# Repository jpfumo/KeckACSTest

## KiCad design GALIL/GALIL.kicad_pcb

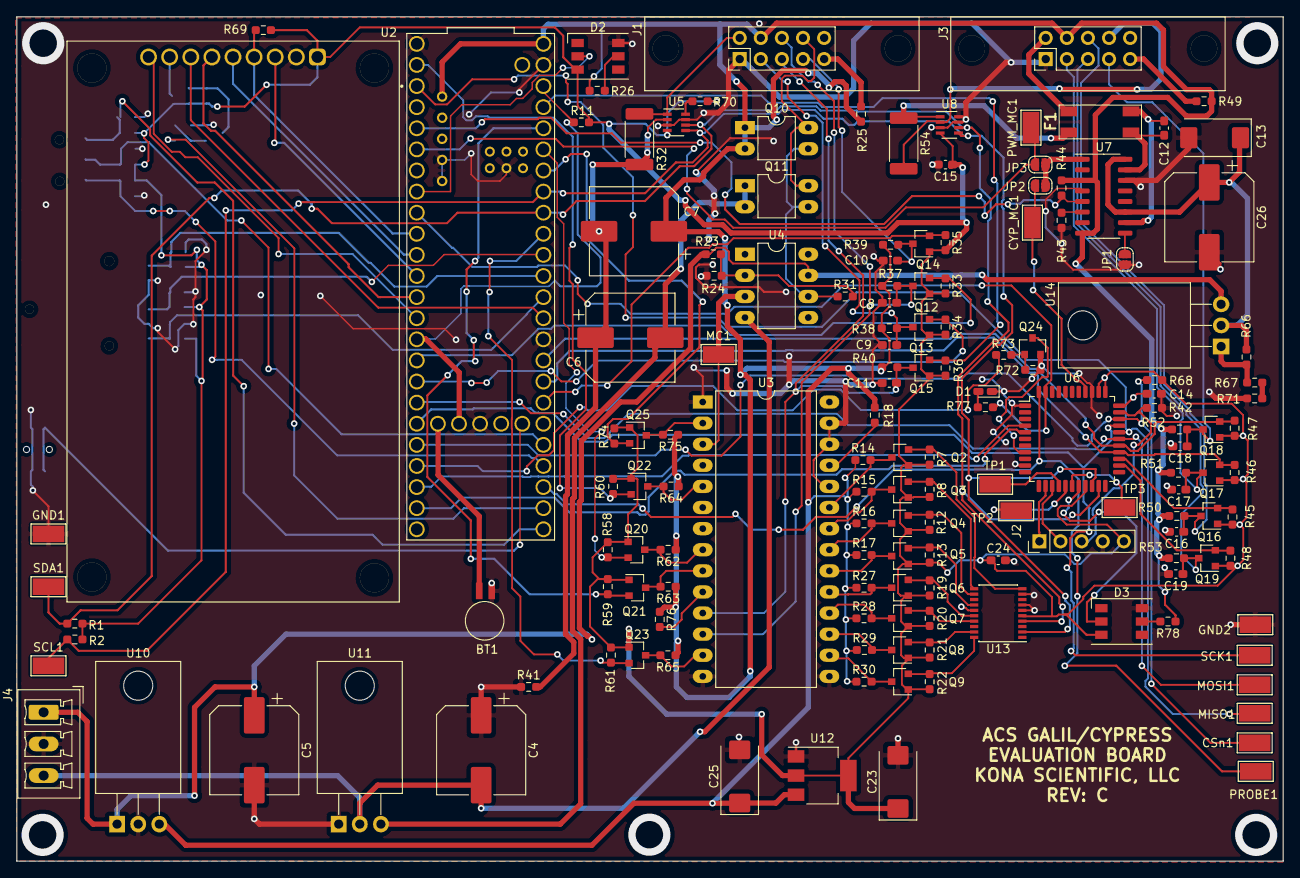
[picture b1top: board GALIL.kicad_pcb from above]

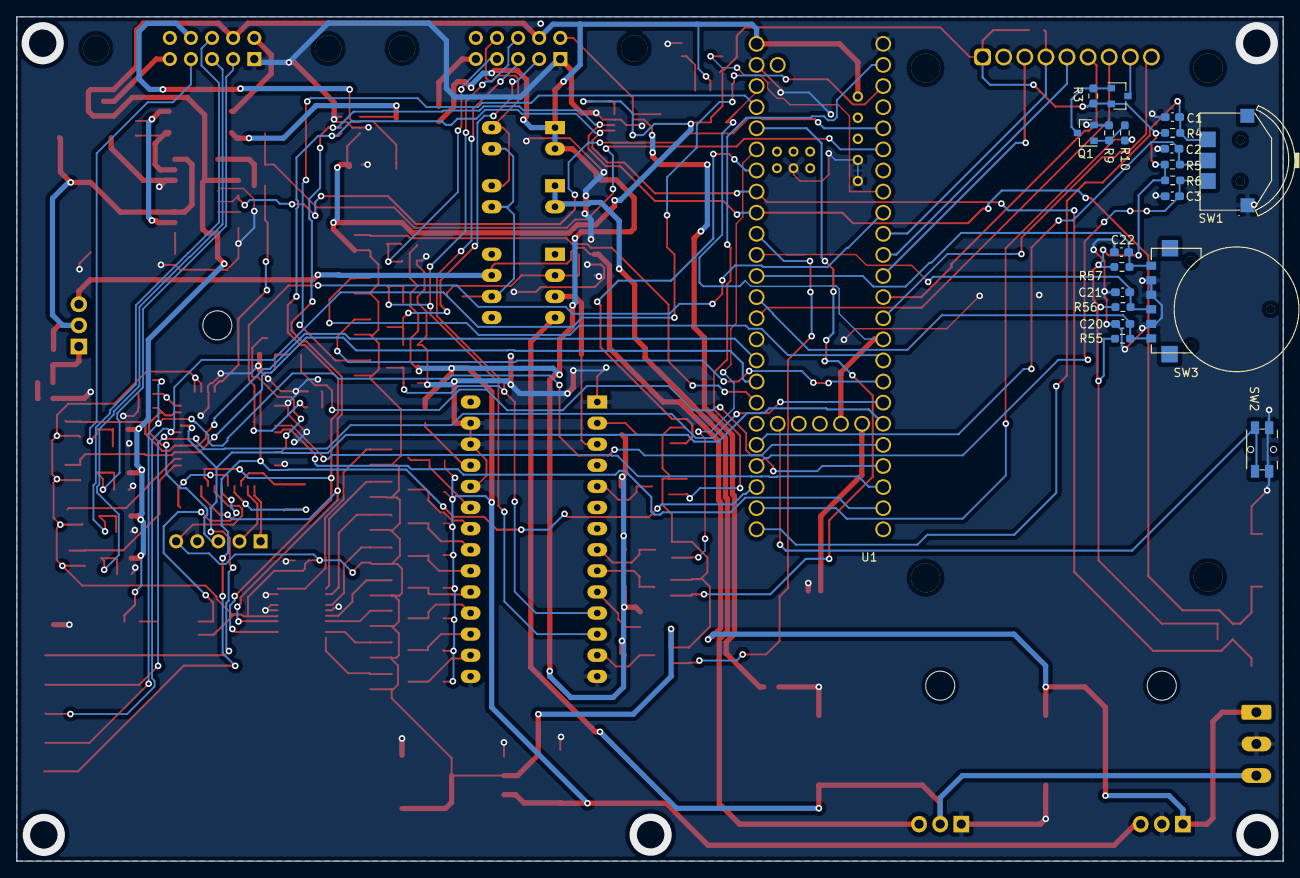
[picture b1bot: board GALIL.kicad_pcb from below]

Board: 2 copper layers, 152.4 x 101.6 mm, 173 parts (21 on the bottom side), 117 nets.

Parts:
BT1: Battery_Cell; BatteryHolder_Seiko_MS621F
C1, C2, C3: 0U1; C_0603_1608Metric_Pad1.08x0.95mm_HandSolder
C4, C5, C6, C7, C26: CP; CP_Elec_10x10.5
C8, C9, C10, C11, C16, C17, C18, C19, C20, C21, C22, C24: C; C_0603_1608Metric_Pad1.08x0.95mm_HandSolder
C12: 2200pF; C_0603_1608Metric_Pad1.08x0.95mm_HandSolder
C13: 740mF; CP_EIA-7343-15_Kemet-W
C14, C15: 1uF; C_0603_1608Metric_Pad1.08x0.95mm_HandSolder
C23, C25: CP; CP_EIA-7343-20_Kemet-V_Pad2.25x2.55mm_HandSolder
CSn1: CSn; TestPoint_Keystone_5019_Minature
CYP_MC1: TestPoint; TestPoint_Keystone_5019_Minature
D1: LED; LED_0603_1608Metric_Castellated
D2, D3: WS2812S; LED_WS2812_PLCC6_5.0x5.0mm_P1.6mm
F1: 744229; WE-SL575
GND1, GND2: TestPoint; TestPoint_Keystone_5019_Minature
J1, J3: Conn_01x10; StrutConn
J2: Conn_01x05; PinHeader_1x05_P2.54mm_Vertical
J4: Conn_01x03; PhoenixContact_MCV_1,5_3-G-3.81_1x03_P3.81mm_Vertical
JP1, JP2, JP3: SolderJumper_2_Open; SolderJumper-2_P1.3mm_Open_RoundedPad1.0x1.5mm
MC1: TestPoint; TestPoint_Keystone_5019_Minature
MISO1: MISO; TestPoint_Keystone_5019_Minature
MOSFET1: FDN358P; SOT-23
MOSI1: MOSI; TestPoint_Keystone_5019_Minature
PROBE1: PROBE; TestPoint_Keystone_5019_Minature
PWM_MC1: TestPoint; TestPoint_Keystone_5019_Minature
Q1, Q24: MMBT3904; SOT-23
Q2, Q3, Q4, Q5, Q6, Q7, Q8, Q9, Q12, Q13, Q14, Q15, Q16, Q17, Q18, Q19, Q20, Q21, Q22, Q23, Q25: BSS138; SOT-23
Q10: IRFD110; DIP-4_W7.62mm_LongPads
Q11: IRFD9102; DIP-4_W7.62mm_LongPads
R1, R2: 4K75; R_0603_1608Metric_Pad0.98x0.95mm_HandSolder
R3, R4, R5, R6, R9, R55, R56, R57, R68, R69, R72, R76: 10K0; R_0603_1608Metric_Pad0.98x0.95mm_HandSolder
R7, R8, R12, R13, R14, R15, R16, R17, R19, R20, R21, R22, R27, R28, R29, R30, R58, R59, R60, R61, R62, R63, R64, R65, R74, R75: R; R_0603_1608Metric_Pad0.98x0.95mm_HandSolder
R10, R73: 1K0; R_0603_1608Metric_Pad0.98x0.95mm_HandSolder
R11: DNP; R_0603_1608Metric_Pad0.98x0.95mm_HandSolder
R18, R24, R33, R34, R35, R36, R37, R38, R39, R40, R42, R44, R45, R46, R47, R48, R50, R51, R52, R53, R70: 10K; R_0603_1608Metric_Pad0.98x0.95mm_HandSolder
R23: 130K; R_0603_1608Metric_Pad0.98x0.95mm_HandSolder
R25, R49, R77: 120ohms 1/4W; R_0603_1608Metric_Pad0.98x0.95mm_HandSolder
R26, R78: 100R0; R_0603_1608Metric_Pad0.98x0.95mm_HandSolder
R31: 68K; R_0603_1608Metric_Pad0.98x0.95mm_HandSolder
R32: 1R0; R_2512_6332Metric_Pad1.40x3.35mm_HandSolder
R41: 0R0; R_0603_1608Metric_Pad0.98x0.95mm_HandSolder
R43: 5K; R_0603_1608Metric_Pad0.98x0.95mm_HandSolder
R54: 1.0; R_2512_6332Metric_Pad1.40x3.35mm_HandSolder
R66: 120; R_0603_1608Metric_Pad0.98x0.95mm_HandSolder
R67: 906; R_0603_1608Metric_Pad0.98x0.95mm_HandSolder
R71: 54; R_0603_1608Metric_Pad0.98x0.95mm_HandSolder
SCK1: SCK; TestPoint_Keystone_5019_Minature
SCL1: SCL; TestPoint_Keystone_5019_Minature
SDA1: SDA; TestPoint_Keystone_5019_Minature
SW1: SEL_SW
SW2: SW_Push; Panasonic_EVQPUL_EVQPUC
SW3: EVQ-WKA001
TP1, TP2, TP3: TP; TestPoint_Keystone_5019_Minature
U1: DEV-16771; teensy41
U2: TFT_LCD; TFT_DISP_2P2
U3: GALIL; DIP-28_W15.24mm_LongPads
U4: TL081; DIP-8_W7.62mm_LongPads
U5, U8: INA219AxDCN; SOT-23-8
U6: CY8C4245AXI-483; LQFP-44_10x10mm_P0.8mm
U7: SI8244; SO-16_3.9x9.9mm_P1.27mm
U10: LM7805_TO220; TO-220-3_Horizontal_TabDown
U11: LM7905_TO220; TO-220-3_Horizontal_TabDown
U12: LT1117-3.3; SOT-223-3_TabPin2
U13: PCF8574ATS; SSOP-20_4.4x6.5mm_P0.65mm
U14: LM350_TO220; TO-220-3_Horizontal_TabDown

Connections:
+3V3: C15.1, C23.1, C24.1, D2.3, D3.3, J2.5, MOSFET1.2, Q2.1, Q3.1, Q4.1, Q5.1, Q6.1, Q7.1, Q8.1, Q9.1, Q12.1, Q13.1, Q14.1, Q15.1, Q16.1, Q17.1, Q18.1, Q19.1, Q20.1, Q21.1, Q22.1, Q23.1, Q25.1, R1.1, R2.1, R3.1, R4.1, R5.1, R6.1, R7.1, R8.1, R11.1, R12.1, R13.1, R19.1, R20.1, R21.1, R22.1, R33.2, R34.2, R35.2, R36.2, R45.2, R46.2, R47.2, R48.2, R55.2, R56.2, R57.2, R58.1, R59.1, R60.1, R61.1, R68.1, R69.1, R70.2, R74.1, U2.1, U5.4, U6.19, U6.34, U6.35, U8.4, U12.2, U13.5
+5V: C7.1, C25.1, J1.4, J3.4, Q10.1, Q10.2, R14.1, R15.1, R16.1, R17.1, R18.2, R25.1, R26.1, R27.1, R28.1, R29.1, R30.1, R37.2, R38.2, R39.2, R40.2, R44.1, R49.1, R50.2, R51.2, R52.2, R53.2, R62.1, R63.1, R64.1, R65.1, R75.1, R76.1, R78.1, U1.5V, U1.VIN, U7.3, U7.8, U10.3, U12.3
+15V: C5.1, J4.1, R23.2, U4.7, U10.1, U14.3
-5V: C6.2, Q11.1, Q11.2, U11.3
-15V: C4.2, J4.3, U4.4, U11.2
BL_EN: MOSFET1.1, Q1.3, R3.2
CLED: D3.2, U6.18
CS: U1.10, U2.3
CYPRESS_PWM0: CYP_MC1.1, JP2.2, U6.37
CYP_CSn: CSn1.1, R68.2, U1.28, U6.31
CypressRST_MOT0: Q24.3, U6.8
Cypress_DebugReset0: J2.3, R42.1, U6.32
DC: U1.9, U2.5
ENC1_A: C19.1, J3.5, Q19.3, R53.1
ENC1_A_L: Q19.2, R48.1, U6.24
ENC1_B: C16.1, J3.6, Q16.3, R50.1
ENC1_B_L: Q16.2, R45.1, U6.25
ENC1_HOME: C17.1, J3.3, Q17.3, R51.1
ENC1_HOME_L: Q17.2, R46.1, U1.40, U6.26
ENC1_HOME_OUT: U1.30, U6.4
ENC1_INDEX: C18.1, J3.7, Q18.3, R52.1
ENC1_INDEX_L: Q18.2, R47.1, U1.41, U6.27
ENC1_INDEX_OUT: U1.31, U6.5
ENC1_MTR1: F1.3, R54.1, U8.1
ENC1_MTR2: F1.4, J3.2
ENC1_MTR_RTN: JP1.1, U7.9
ENC2_A: C11.1, J1.5, Q15.3, R40.1, U3.11
ENC2_A_L: Q15.2, R36.1, U1.23
ENC2_B: C8.1, J1.6, Q12.3, R37.1, U3.12
ENC2_B_L: Q12.2, R33.1, U1.24
ENC2_HOME: C9.1, J1.3, Q13.3, R38.1
ENC2_HOME_L: Q13.2, R34.1, U1.25
ENC2_INDEX: C10.1, J1.7, Q14.3, R39.1
ENC2_INDEX_L: Q14.2, R35.1, U1.39
ENC2_MTR1: J1.8, Q10.4, Q11.4
ENC2_MTR2: J1.2, R32.1, U5.1
GALIL_CLK: Q22.2, R60.2, U1.0
GALIL_CLK_HV: Q22.3, R64.2, U3.5
GALIL_DEC: Q20.2, R58.2, U1.21
GALIL_DEC_HV: Q20.3, R62.2, U3.8
GALIL_ERR_FLG: Q25.2, R74.2, U1.20
GALIL_ERR_FLG_HV: Q25.3, R75.2, U3.2
GALIL_INC: Q21.2, R59.2, U1.22
GALIL_INC_HV: Q21.3, R63.2, U3.9
GALIL_PE0: Q2.2, R7.2, U13.10
GALIL_PE1: Q3.2, R8.2, U13.11
GALIL_PE2: Q4.2, R12.2, U13.12
GALIL_PE3: Q5.2, R13.2, U13.14
GALIL_PE4: Q6.2, R19.2, U13.16
GALIL_PE5: Q7.2, R20.2, U13.17
GALIL_PE6: Q8.2, R21.2, U13.19
GALIL_PE7: Q9.2, R22.2, U13.20
GALIL_RSTn: Q23.2, R61.2, U1.17
GALIL_RSTn_HV: Q23.3, R65.2, U3.13
GND: BT1.2, C1.1, C2.1, C3.1, C4.1, C5.2, C8.2, C9.2, C10.2, C11.2, C13.2, C14.1, C15.2, C16.2, C17.2, C18.2, C19.2, C20.2, C21.2, C22.2, C23.2, C24.2, C25.2, C26.2, D1.1, D2.6, D3.6, GND1.1, GND2.1, J1.1, J2.4, J3.1, J4.2, JP1.2, Q1.2, Q24.2, R9.2, R24.1, R41.1, R42.2, R43.2, R71.2, R72.2, SW1.5, SW2.1, SW3.2, SW3.3, SW3.5, U1.GND1, U1.GND2, U1.GND3, U1.GND4, U1.GND5, U1.USB_GND1, U1.USB_GND2, U2.2, U3.1, U3.14, U3.15, U3.24, U3.26, U3.27, U5.3, U5.7, U6.1, U6.10, U6.36, U7.4, U7.14, U8.3, U8.7, U8.8, U10.2, U11.1, U12.1, U13.6, U13.7, U13.9, U13.15
GNDPWR: C6.1, C7.2, R32.2, R41.2, U5.2
HV_GALIL_PE0: Q2.3, R14.2, U3.23
HV_GALIL_PE1: Q3.3, R15.2, U3.22
HV_GALIL_PE2: Q4.3, R16.2, U3.21
HV_GALIL_PE3: Q5.3, R17.2, U3.20
HV_GALIL_PE4: Q6.3, R27.2, U3.19
HV_GALIL_PE5: Q7.3, R28.2, U3.18
HV_GALIL_PE6: Q8.3, R29.2, U3.17
HV_GALIL_PE7: Q9.3, R30.2, U3.16
I2C_SCL: R2.2, SCL1.1, U1.19, U5.5, U6.20, U8.5, U13.2
I2C_SDA: R1.2, SDA1.1, U1.18, U5.6, U6.21, U8.6, U13.4
LED: R77.2, U1.7, U6.43
MISO: U1.12, U2.9
MISO1: MISO1.1, U1.1, U6.29
MOSI: U1.11, U2.6
MOSI1: MOSI1.1, U1.26, U6.28
Motor_Cntrl: MC1.1, U3.3, U4.3
NEOPIXEL: D2.2, U1.6
unnamed: BT1.1, U1.VBAT
unnamed: C12.1, F1.1, U7.10
unnamed: C12.2, F1.2, U7.15
unnamed: C14.2, U6.33
unnamed: D1.2, R77.1
unnamed: D2.5, R26.2
unnamed: D3.5, R78.2
unnamed: J1.9, R25.2
unnamed: J2.1, U6.13
unnamed: J2.2, U6.14
unnamed: J3.8, R54.2, U8.2
unnamed: J3.9, R49.2
unnamed: JP2.1, JP3.1, U7.1
unnamed: MOSFET1.3, U2.8
unnamed: Q1.1, R9.1, R10.2
unnamed: Q10.3, Q11.3, R31.1, U4.6
unnamed: Q24.1, R72.1, R73.2
unnamed: R10.1, U1.34
unnamed: R11.2, U1.3.3V_1, U1.3.3V_2, U1.3.3V_3
unnamed: R18.1, U3.25
unnamed: R23.1, R24.2, R31.2, U4.2
unnamed: R43.1, U7.6
unnamed: R66.2, R67.2, U14.1
unnamed: R67.1, R71.1
unnamed: R70.1, U5.8
unnamed: R73.1, U1.29
unnamed: R76.2, U3.10
unnamed: SW2.2, U1.ON/OFF
unnamed: TP1.1, U6.15
unnamed: TP2.1, U6.16
unnamed: TP3.1, U6.17
PROBE: PROBE1.1, U1.35, U6.44
PWM_DISABLE_MOT0: R44.2, U1.3, U7.5
PWM_MC: JP3.2, PWM_MC1.1, U1.4
ROT_A: C22.1, R57.1, SW3.1, U1.15
ROT_B: C20.1, R55.1, SW3.6, U1.14
ROT_SEL: C21.1, R56.1, SW3.4, U1.16
RSTn: R69.2, U1.8, U2.4
SCK: U1.13, U2.7
SCK1: SCK1.1, U1.27, U6.30
SW_DWN: C3.2, R6.2, SW1.4, U1.36
SW_SEL: C2.2, R5.2, SW1.3, U1.37
SW_UP: C1.2, R4.2, SW1.2, U1.33
V_MOTOR: C13.1, C26.1, R66.1, U7.11, U7.16, U14.2

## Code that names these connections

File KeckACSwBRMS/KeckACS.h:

// Main header file for project
#ifndef _KECK_ACS_H
#define _KECK_ACS_H

// Switches to turn on certain debug messaging
//#define DEBUG_MENUS 
#define DEBUG_GALIL
//#define DEBUG_CYPRESS 
//#define DEBUG_SWITCHES



// CLI
//Create a 32 bytes static buffer to be used exclusive by SerialCommands object.
//The size should accomodate command token, arguments, termination sequence and string delimeter \0 char.
char serial_command_buffer_[32];

//Creates SerialCommands object attached to Serial
//working buffer = serial_command_buffer_
//command delimeter: Cr & Lf
//argument delimeter: SPACE
SerialCommands serial_commands_(&Serial, serial_command_buffer_, sizeof(serial_command_buffer_), "\n", " ");




typedef enum {
  CW, 
  CCW
  } dtype_t;

typedef enum {
  PAGE_TOP, 
  PAGE_GALIL, 
  PAGE_CYPRESS, 
  PAGE_CYPREPLY
  } ptype_t;

typedef enum {
  HOME, 
  STEPS, 
  TOTAL, 
  MAX, 
  CLEAR, 
  CYCLES, 
  ELAPSED, 
  ERR, 
  APCREG, 
  RECORD, 
  MGO, 
  MEXIT
  } mtype_t;
  
typedef enum {
  label = -1, 
  funcall, 
  selectable, 
  editable, 
  noneditable, 
  myexit
  } itype_t;

// label, static label, does nothing
// funcall, goto this function &function_name
// selectable, Goto to this menu
// editable, Can change the value of this item, used to create an input value
// noneditable, cannot change the value, used to display a value
// myexit, indicates the menu exit point (pagenum =0, itemnum = 0)



#define NUM_LEDS 1

// Pin definitions
#define TFT_DC          9
#define TFT_CS          10
#define TFT_MOSI        11
#define TFT_CLK         13
#define TFT_RST         8
#define TFT_MISO        12
#define buttonUpPin     33
#define buttonDownPin   36
#define buttonSelectPin 37
#define backlight_EN    34
#define encoder0PinA    15
#define encoder0PinB    14
#define encoder0Btn     16
#define CypressCSPin    28

#define GALIL_RST       17
#define GALIL_CLK       0
#define GALIL_DEC       21
#define GALIL_INC       22
#define GALIL_IDX       39
#define GALIL_HOM       25
#define GALIL_B         24
#define GALIL_A         23
#define GALIL_ERRn      20

#define PROBE           35

#define Cypress_RSTn 35
#define Cypress_HOM 40
#define Cypress_IDX 41
#define PWM_DISABLE_MOT0 3


// GALIL
#define GALIL_MAX_STEP 2048

static float current_mA = 0;
static int16_t rawcurrent;
volatile bool galil_err;
bool Galil_SlowFlag = false;
bool GalilEnable = false;

// CYPRESS
#define CYPRESS_KP 0.9
#define CYPRESS_KI 20.0
#define CYPRESS_KD 0.008

/* --------------------------------------------------------------------- 
 * SPI MESSAGING
 * --------------------------------------------------------------------- */
/* V2 protocol 

   1) Messages have opcodes (configuration, position, get status)
   2) Messages are validated by a checksum instead of an arbitrary signature pattern.
   3) Transfer the max message size every time, regardless of all bytes used or not.
*/
    
/* Set this to match the size of the status response message, 21 bytes */    
#define MAX_MESSAGE_SIZE 21
    
/* Opcodes that can come from the node box software */
typedef enum {
    opUNDEFINED = 0,
    opConfig    = 1,
    opStatus    = 2,
    opSetEnc    = 3,
    opMAX       
} txMessage_opcodes_t;    

/* Sanity check for opcodes */
#define txMessageOpcodeValid(op) ( ((txMessage_opcodes_t) op > opUNDEFINED) && ((txMessage_opcodes_t) op < opMAX) )

typedef struct { 
    uint8_t checksum;        
    uint8_t size;       /* Size of the message bytes, including opcode and size and checksum */
    uint8_t opcode;     /* Operation (generic overlay for previewing opcode value) */
} __attribute__ ((__packed__)) txMessage_overlay_t;

/* Configuration message, 19 bytes */
typedef struct {
    uint8_t checksum;        
    uint8_t size;       /* Size of the message bytes, including opcode and size and checksum */
    uint8_t opcode;     /* Operation: 01 == config */        
    uint8_t sequence;   /* Configuration message sequence number */
    float Kp;         /* PID constants to be used in calculation */
    float Ki;
    float Kd;
    uint8_t limit_Total;/* Total drive output limit, +/- percentage */
    uint8_t limit_ITerm;/* PID I term output limit, also +/- percentage */
    uint8_t effsetdelta;/* PID effective setpoint increment delta, nominally 25 steps */
} __attribute__ ((__packed__)) txMessage_config_t;

/* Status message, contains desired position and such values, 10 bytes */
typedef struct {
    uint8_t  checksum;        
    uint8_t  size;       /* Size of the message bytes, including opcode and size and checksum */
    uint8_t  opcode;     /* Operation: 02 == status */
    uint8_t  enable;     /* Enable/disable PID algorithm */
    int32_t  setpoint;   /* Setpoint (desired actuator position) */
    int8_t   jog;        /* Jog value, to manually move the motor; valid range -100 to 100 */ 
    uint8_t  clearfaults;/* Set to nonzero to clear all the current faults */
} __attribute__ ((__packed__)) txMessage_status_t;
   
/* Clear message, contains new encoder position, 7 bytes */
typedef struct {
    uint8_t  checksum;        
    uint8_t  size;       /* Size of the message bytes, including opcode and size and checksum */
    uint8_t  opcode;     /* Operation: 03 == set encoders */
    uint32_t  setpoint;   /* Setpoint (force an actuator logical position) */
} __attribute__ ((__packed__)) txMessage_setenc_t;


/* Wrap the message with an array of bytes */
union {
    uint8_t             buf[MAX_MESSAGE_SIZE];
    txMessage_overlay_t overlay;
    txMessage_config_t  config;
    txMessage_status_t  status;  
    txMessage_setenc_t  setenc;
} txMessage, txMessageCopy;

/* Message back to the BBB, watch out for alignment here by packing the structure (should be 18 bytes) */
typedef struct  {  
    uint8_t  checksum;   /* Message checksum */    
    uint8_t  version0;   /* Version byte 0 */ 
    uint8_t  version1;   /* Version byte 1 */
    uint8_t  version2;   /* Version byte 2 */
    uint8_t  size;       /* Size of the message bytes, including opcode and size and checksum */
    uint8_t  opcode;     /* Echo back of the opcode this response is for, operation: 02 == status */
    uint8_t  state;      /* Enum value for current device configuration state */ 
    uint8_t  fault;      /* Bit encoded fields for current fault status */
    uint8_t  sequence;   /* Echo back the config sequence number currently set */
    uint16_t checksum_errors; /* Count of checksum errors */
    int16_t current;     /* Motor current consumption (mA) */
    int32_t position;    /* Actual actuator position, signed value */ 
    float pwm;         /* PWM value the motor is moving at */     
} __attribute__ ((__packed__)) rxMessage_t;

/* Wrap the message with an array of bytes */
union {    
    uint8_t       buf[MAX_MESSAGE_SIZE];
    rxMessage_t msg;
} rxMessage;

/* Some globals for the Cypress */
uint8_t CypressPIDEnable = 0;
bool CypressReinit = false;
bool CypressEnable = false;
int32_t CypressPosition, LastCypressPosition, CypressDestination = 0;
uint8_t CypressSequence = 0;
uint8_t CypressState = 0;
float CypressPWM = 0.0;
bool CypressRecording = false;
bool CypressInmotion = false;
bool CypressWriteFile = false;
uint32_t CypressStartTime = 0;
uint32_t CypressEndTime = 0;
int16_t CypressCurrent = 0;


#endif

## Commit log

2022-08-08 Split sketch into multiple files
    Work-in-progress of splitting sketch into multiple files and cleanup/clarification of code.
2022-08-10 Add CLI
    Initial changes to add a CLI to the serial interface for external automation, more code cleanup/movement.
2022-08-12 Checkpoint
    Added new SD card writing interface that auto-increments filenames based on what's on the card. Added 100ms oversample to data capture. Converted captured data to JSON before writing to disk. More ge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
2022-08-20 Checkpoint
    Implemented controls for Cypress device.
2022-08-20 Checkpoint2
    Second checkpoint of the day. Fix timestamps of Cypress recording.
2022-08-22 Checkpoint3
    Debugging recording functions.
2022-10-06 Create GALILExercise.ino
    Test code for just the Galil side.
2022-12-20 Add files via upload
    Latest ACS TEST Code port (Fumo port to Paul's code)
